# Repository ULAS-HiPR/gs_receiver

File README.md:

# Groundstation

Groundstation is the receiver/display side of the Ogma system. It is not part of the flight stack itself; it receives telemetry from Ogma and gives the operator a local display. The longer-term plan is for Ogma Console to switch into groundstation mode when this board is connected to a laptop.

## Role In Ogma

- Receives telemetry from the flight stack radio path.
- Displays useful field data locally.
- Provides a future high-detail laptop telemetry view through Ogma Console.

## Current Firmware

Current firmware is CircuitPython code in `firmware/`:

- `code.py`: main display loop.
- `gps_data.py`: GPS data container/parser.
- `screens.py`: ST7789 display screens for GPS/radio status.
- `sx1272.py`: polling SX1272 receive driver.
- `telemetry_protocol.py`: CRC-checked Ogma radio protocol decoder.

The receiver decodes Teachtaire protocol v1, updates the local GPS display, and prints USB serial lines directly consumable by Ogma Console:

- GPS as JSONL.
- CAN as `123#AABBCC...`.
- receiver diagnostics as ignored `#OGMA` comments.

PCB pin map used by firmware: shared SPI, TFT CS/DC/reset `D5/D4/D10`, radio CS/reset `D9/D2`, radio RX/TX switches `A0/A1`.

## Hardware

The repo contains hardware for:

- mobile receiver board,
- SPI display adapter,
- UART adapter.

## Ogma Console Support

Ogma Console can capture mixed GPS/CAN telemetry from the board's CircuitPython USB serial port, decode canonical CAN frames, plot telemetry, and save local bundles. Hardware RF/USB validation remains in the HIL campaign.

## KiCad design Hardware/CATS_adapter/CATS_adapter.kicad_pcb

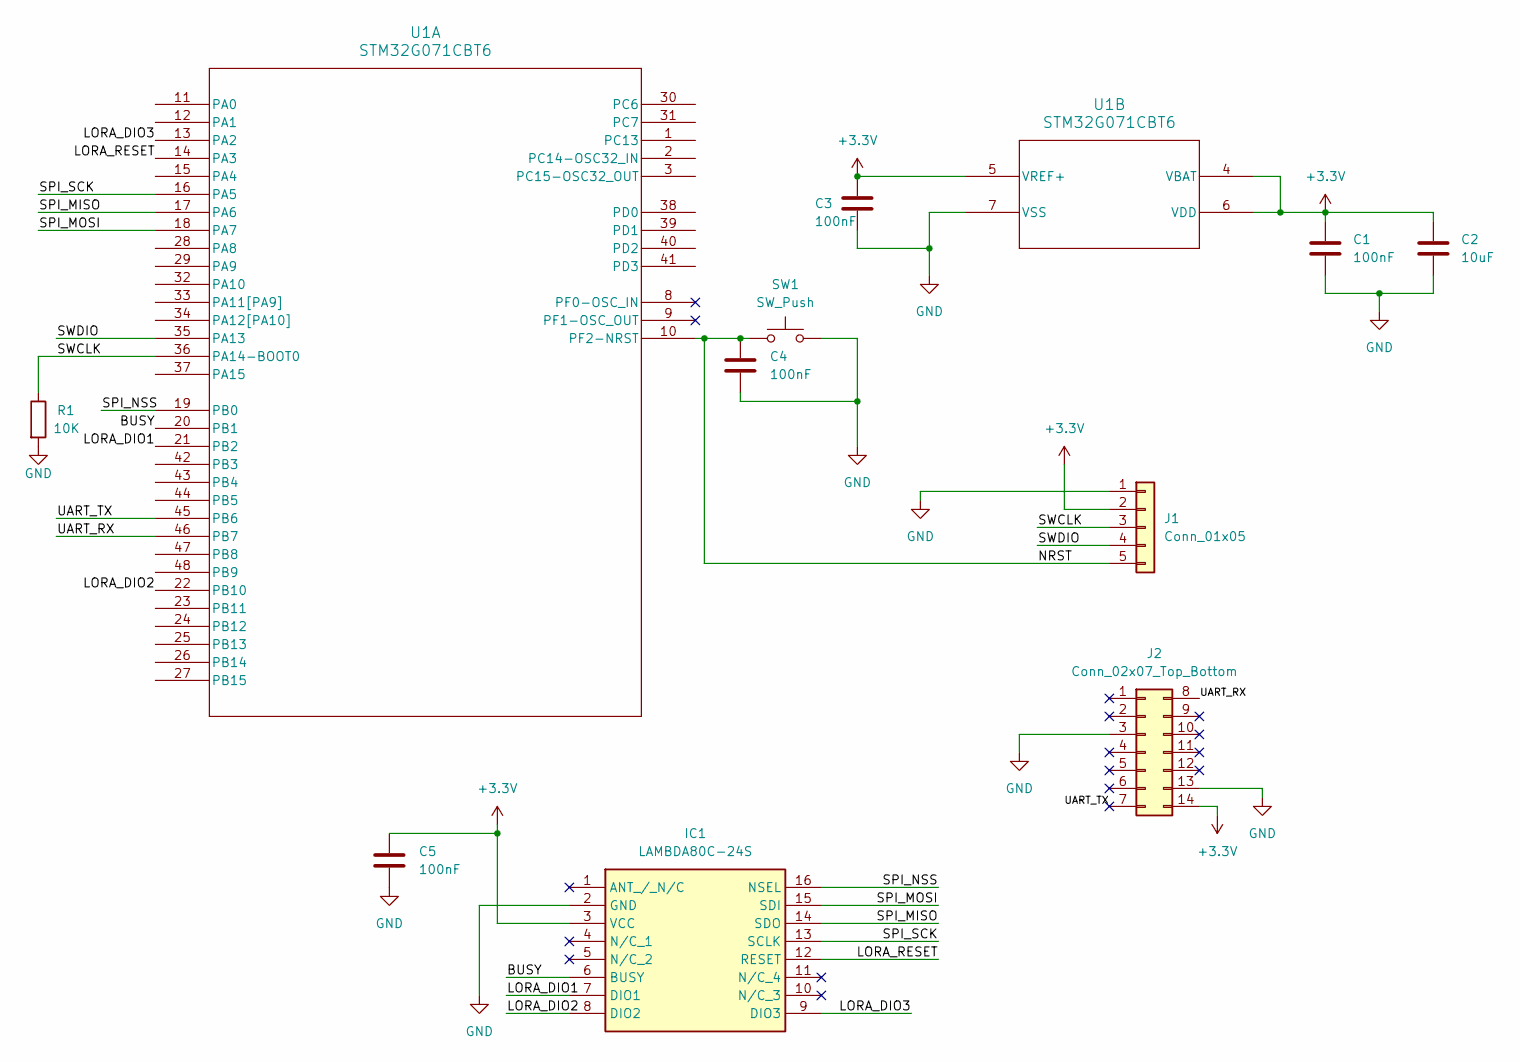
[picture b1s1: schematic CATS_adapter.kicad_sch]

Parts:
C1, C3, C4, C5: 100nF; C_0805_2012Metric_Pad1.18x1.45mm_HandSolder
C2: 10uF; C_0805_2012Metric_Pad1.18x1.45mm_HandSolder
IC1: LAMBDA80C-24S; LAMBDA80C24S; Mouser Part Number 223-LAMBDA80C-24S
J1: Conn_01x05; PinHeader_1x05_P2.54mm_Vertical
J2: Conn_02x07_Top_Bottom; PinHeader_2x07_P2.54mm_Horizontal
R1: 10K; R_0805_2012Metric_Pad1.20x1.40mm_HandSolder
SW1: SW_Push; SW_Push_1P1T_NO_E-Switch_TL3301NxxxxxG
U1: STM32G071CBT6; LQFP-48_7x7mm_P0.5mm

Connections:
+3.3V: C1.1, C2.1, C3.1, C5.1, IC1.3 (VCC), J1.2, J2.14, U1.4 (VBAT), U1.5 (VREF+), U1.6 (VDD)
/BUSY: IC1.6 (BUSY), U1.20 (PB1)
/LORA_DIO1: IC1.7 (DIO1), U1.21 (PB2)
/LORA_DIO2: IC1.8 (DIO2), U1.22 (PB10)
/LORA_DIO3: IC1.9 (DIO3), U1.13 (PA2)
/LORA_RESET: IC1.12 (RESET), U1.14 (PA3)
/NRST: C4.1, J1.5, SW1.1, U1.10 (PF2-NRST)
/SPI_MISO: IC1.14 (SDO), U1.17 (PA6)
/SPI_MOSI: IC1.15 (SDI), U1.18 (PA7)
/SPI_NSS: IC1.16 (NSEL), U1.19 (PB0)
/SPI_SCK: IC1.13 (SCLK), U1.16 (PA5)
/SWCLK: J1.3, R1.1, U1.36 (PA14-BOOT0)
/SWDIO: J1.4, U1.35 (PA13)
/UART_RX: J2.8, U1.46 (PB7)
/UART_TX: J2.7, U1.45 (PB6)
GND: C1.2, C2.2, C3.2, C4.2, C5.2, IC1.2 (GND), J1.1, J2.3, J2.13, R1.2, SW1.2, U1.7 (VSS)

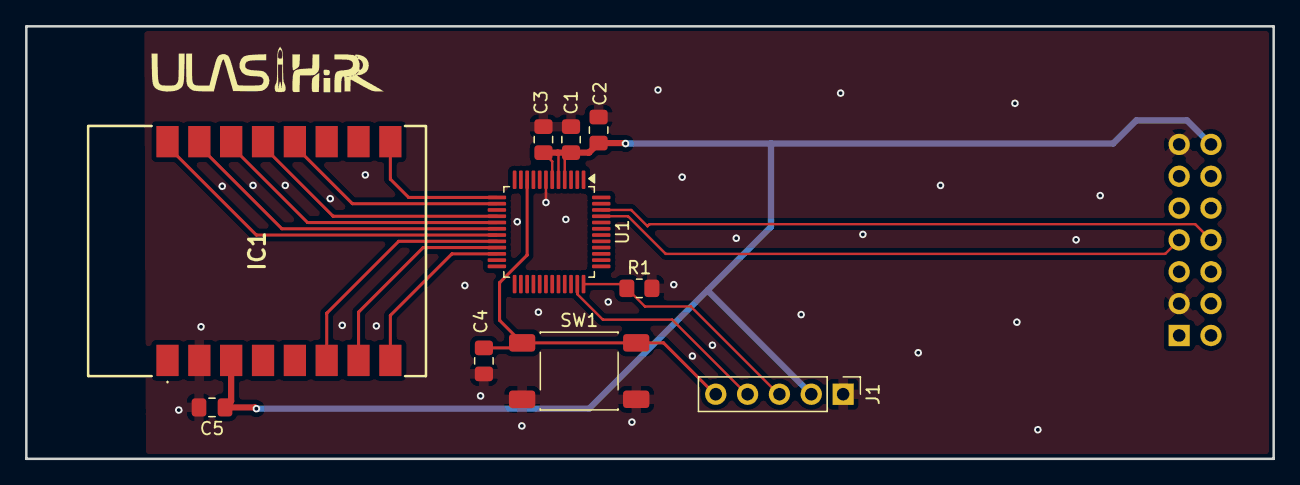
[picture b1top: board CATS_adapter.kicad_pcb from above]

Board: 2 copper layers, 99.5 x 34.5 mm, 11 parts (1 on the bottom side), 16 nets.

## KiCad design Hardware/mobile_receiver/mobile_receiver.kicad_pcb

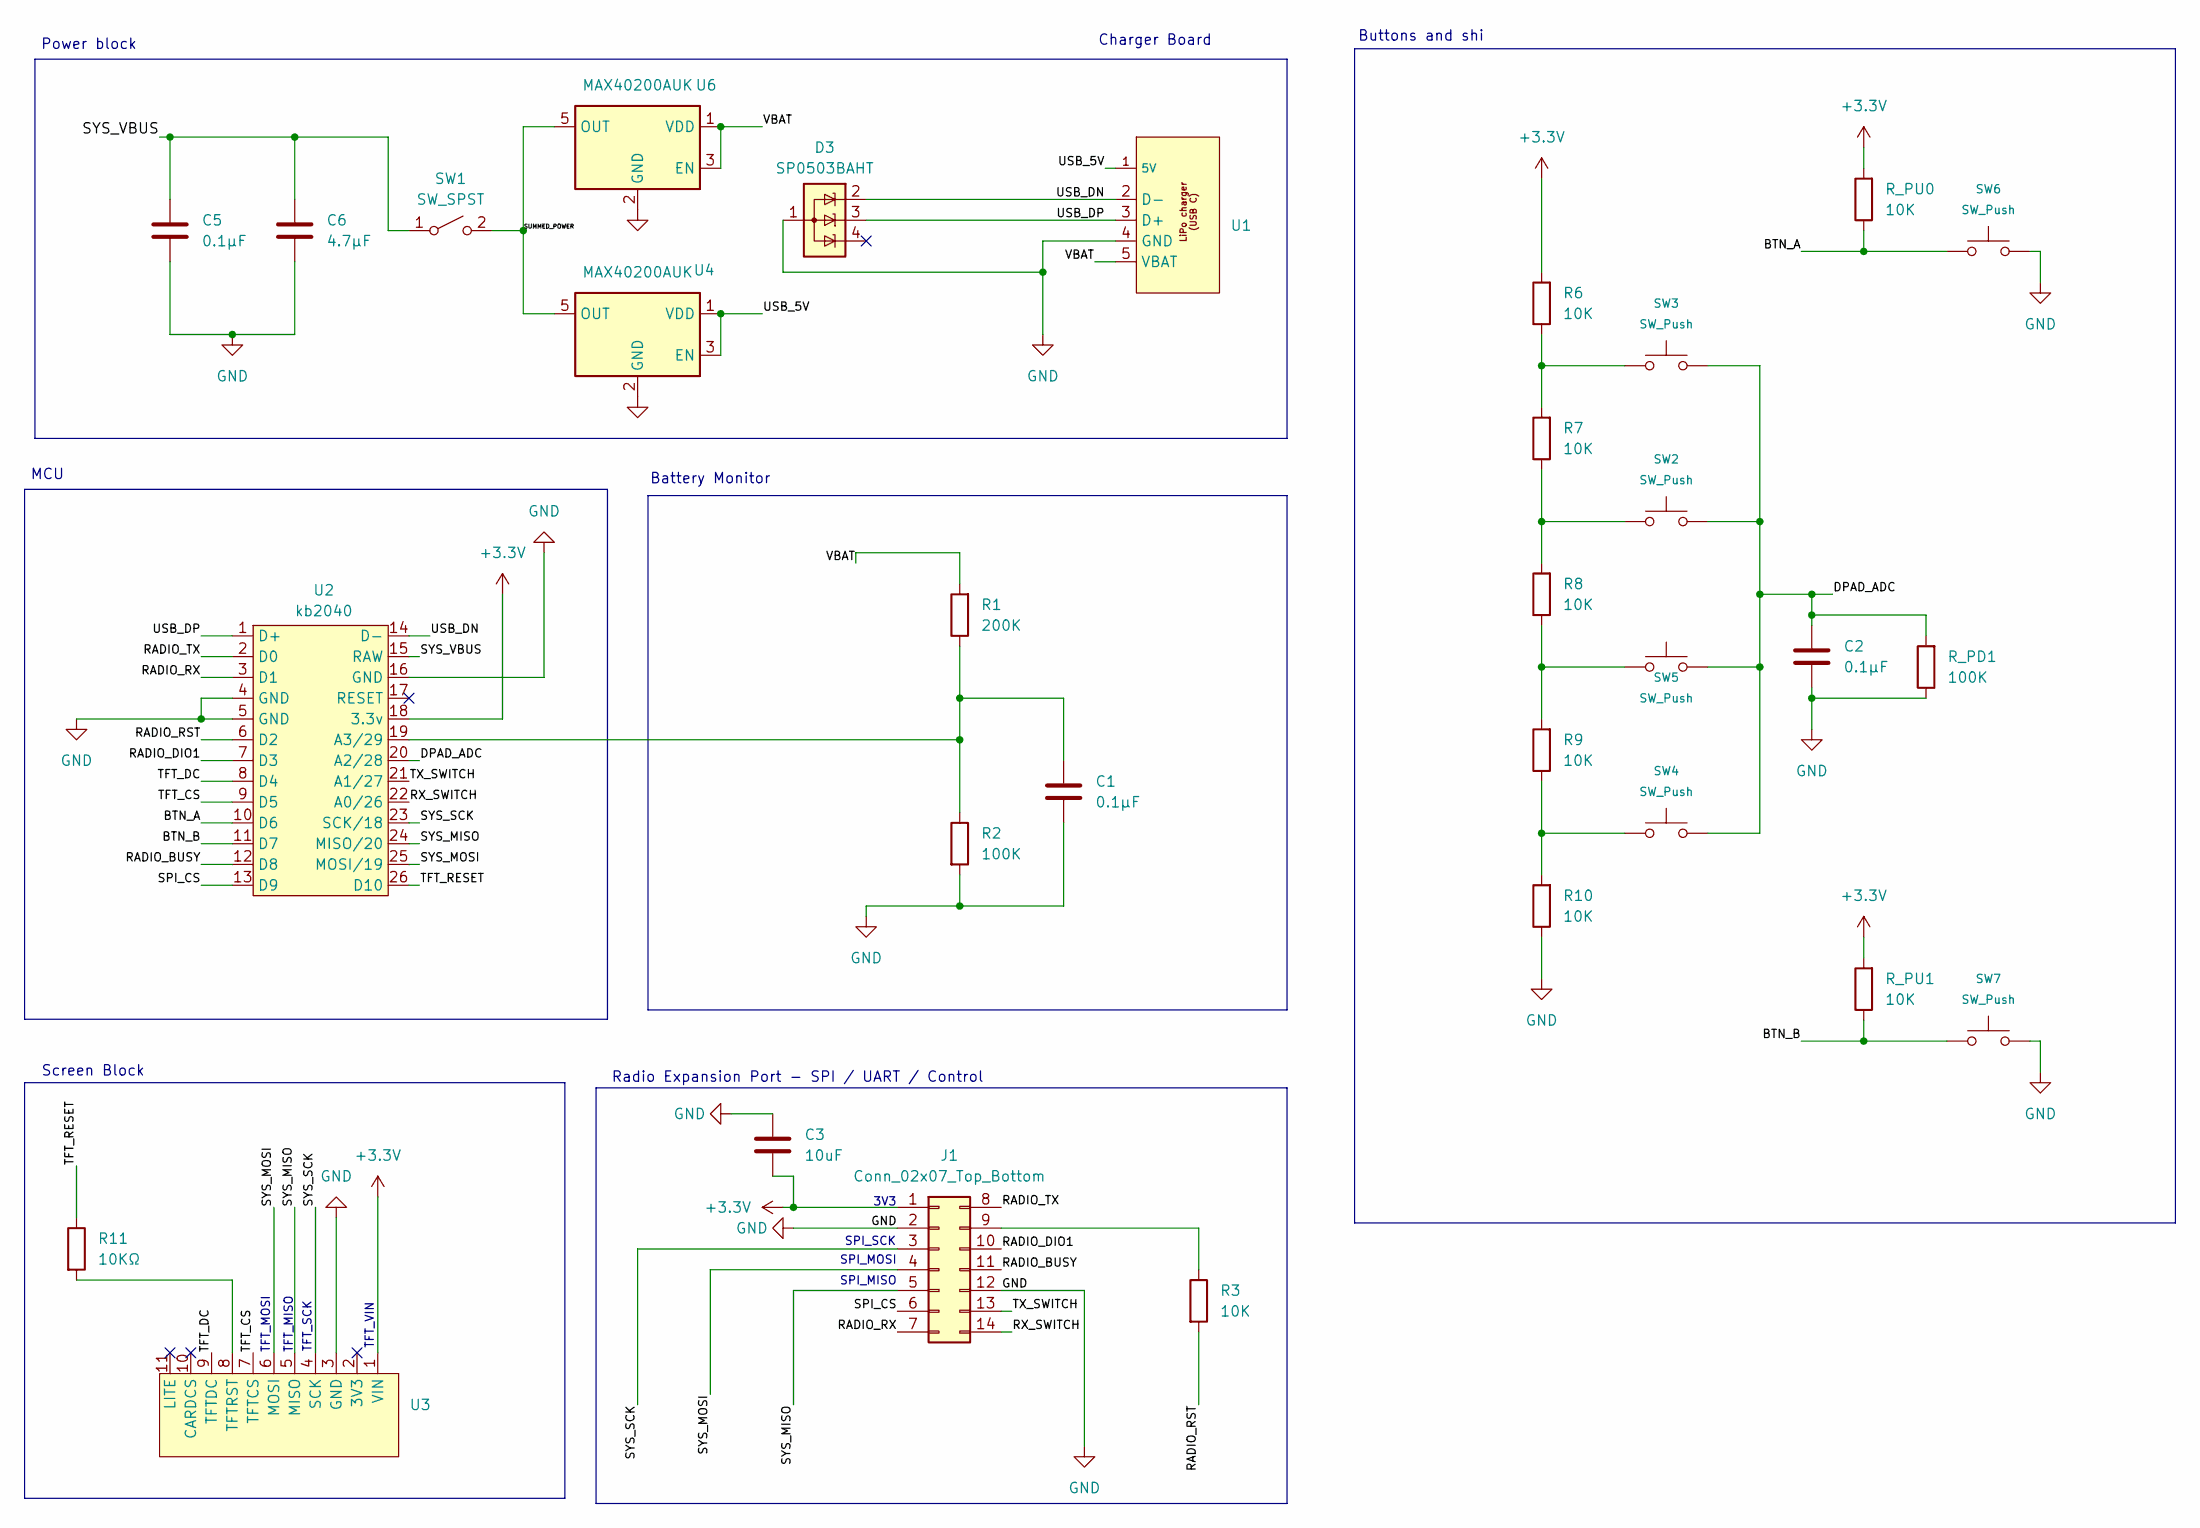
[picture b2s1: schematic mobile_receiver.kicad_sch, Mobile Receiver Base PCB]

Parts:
C1, C2, C5: 0.1µF; C_0805_2012Metric_Pad1.18x1.45mm_HandSolder
C3: 10uF; C_0805_2012Metric_Pad1.18x1.45mm_HandSolder
C6: 4.7µF; C_0805_2012Metric_Pad1.18x1.45mm_HandSolder
D3: SP0503BAHT; SOT-143
J1: Conn_02x07_Top_Bottom; PinSocket_2x07_P2.54mm_Horizontal
R1: 200K; R_0805_2012Metric_Pad1.20x1.40mm_HandSolder
R2: 100K; R_0805_2012Metric_Pad1.20x1.40mm_HandSolder
R3, R6, R7, R8, R9, R10: 10K; R_0805_2012Metric_Pad1.20x1.40mm_HandSolder
R11: 10KΩ; R_0805_2012Metric_Pad1.20x1.40mm_HandSolder
R_PD1: 100K; R_0805_2012Metric_Pad1.20x1.40mm_HandSolder
R_PU0, R_PU1: 10K; R_0805_2012Metric_Pad1.20x1.40mm_HandSolder
SW1: SW_SPST; OS102011MA1QN1_CNK
SW2, SW3, SW4, SW5, SW6, SW7: SW_Push; SW_Push_1P1T_NO_E-Switch_TL3301NxxxxxG
U1: 4410_Micro_LiPo_USBC
U2: kb2040
U3: Adafruit_280X240_Display
U4, U6: MAX40200AUK; SOT-23-5

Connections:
+3.3V: C3.2, J1.1, R6.2, R_PU0.2, R_PU1.2, U2.18 (3.3v), U3.1 (VIN)
/BTN_A: R_PU0.1, SW6.1, U2.10 (D6)
/BTN_B: R_PU1.1, SW7.1, U2.11 (D7)
/DPAD_ADC: C2.1, R_PD1.2, SW2.2, SW3.2, SW4.2, SW5.2, U2.20 (A2/28)
/RADIO_BUSY: J1.11, U2.12 (D8)
/RADIO_DIO1: J1.10, U2.7 (D3)
/RADIO_RST: R3.2, U2.6 (D2)
/RADIO_RX: J1.7, U2.3 (D1)
/RADIO_TX: J1.8, U2.2 (D0)
/RX_SWITCH: J1.14, U2.22 (A0/26)
/SPI_CS: J1.6, U2.13 (D9)
/SUMMED_POWER: SW1.2 (B), U4.5 (OUT), U6.5 (OUT)
/SYS_MISO: J1.5, U2.24 (MISO/20), U3.5 (MISO)
/SYS_MOSI: J1.4, U2.25 (MOSI/19), U3.6 (MOSI)
/SYS_SCK: J1.3, U2.23 (SCK/18), U3.4 (SCK)
/SYS_VBUS: C5.1, C6.1, SW1.1 (A), U2.15 (RAW)
/TFT_CS: U2.9 (D5), U3.7 (TFTCS)
/TFT_DC: U2.8 (D4), U3.9 (TFTDC)
/TFT_RESET: R11.1, U2.26 (D10)
/TX_SWITCH: J1.13, U2.21 (A1/27)
/USB_5V: U1.1 (5V), U4.1 (VDD), U4.3 (EN)
/USB_DN: D3.2 (K), U1.2 (D-), U2.14 (D-)
/USB_DP: D3.3 (K), U1.3 (D+), U2.1 (D+)
/VBAT: R1.2, U1.5 (VBAT), U6.1 (VDD), U6.3 (EN)
GND: C1.2, C2.2, C3.1, C5.2, C6.2, D3.1 (A), J1.2, J1.12, R2.2, R10.1, R_PD1.1, SW6.2, SW7.2, U1.4 (GND), U2.4 (GND), U2.5 (GND), U2.16 (GND), U3.3 (GND), U4.2 (GND), U6.2 (GND)
unnamed: J1.9, R3.1
unnamed: R6.1, R7.2, SW3.1
unnamed: R7.1, R8.2, SW2.1
unnamed: R8.1, R9.2, SW5.1
unnamed: R9.1, R10.2, SW4.1
unnamed: C1.1, R1.1, R2.1, U2.19 (A3/29)
unnamed: R11.2, U3.8 (TFTRST)

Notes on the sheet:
TFT_MOSI
Radio Expansion Port - SPI / UART / Control
3V3
Screen Block
TFT_SCK
MCU
Buttons and shi
TFT_MISO
TFT_VIN
Battery Monitor
SPI_MOSI
SPI_SCK
Charger Board
SPI_MISO
Power block

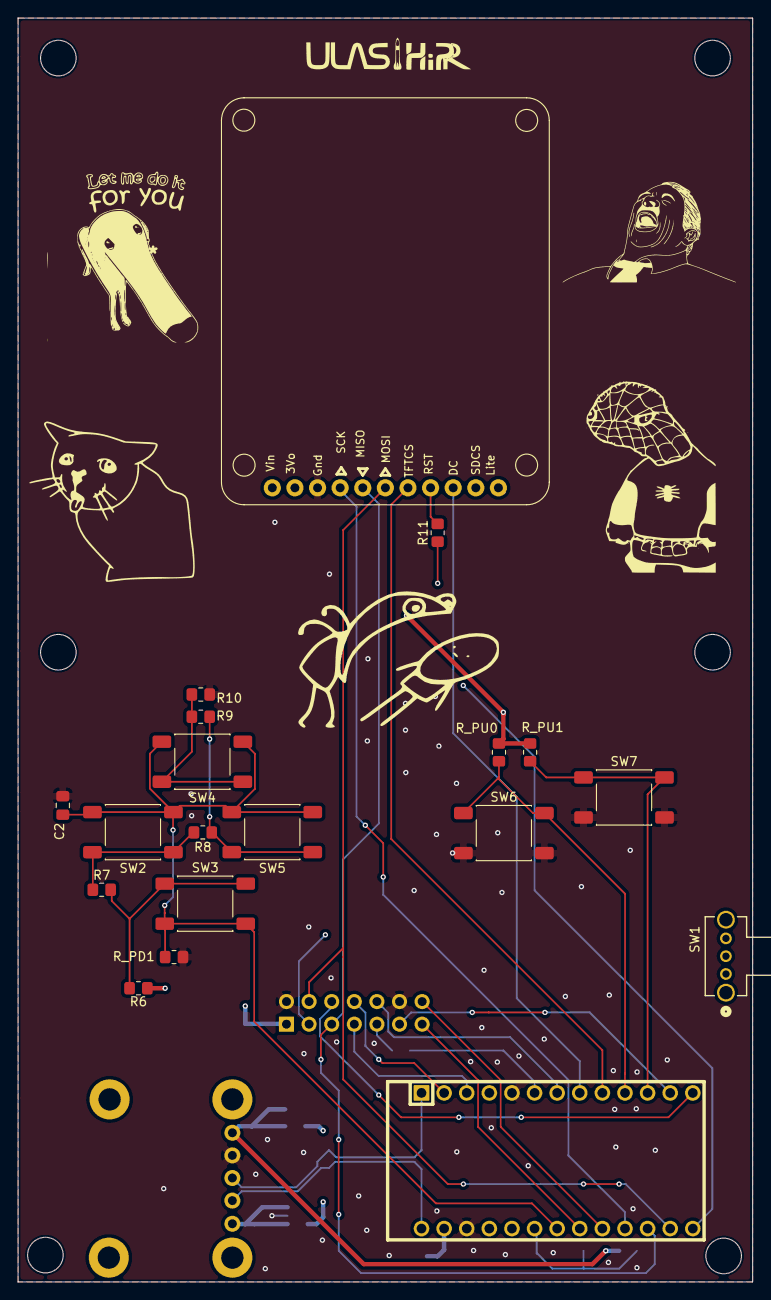
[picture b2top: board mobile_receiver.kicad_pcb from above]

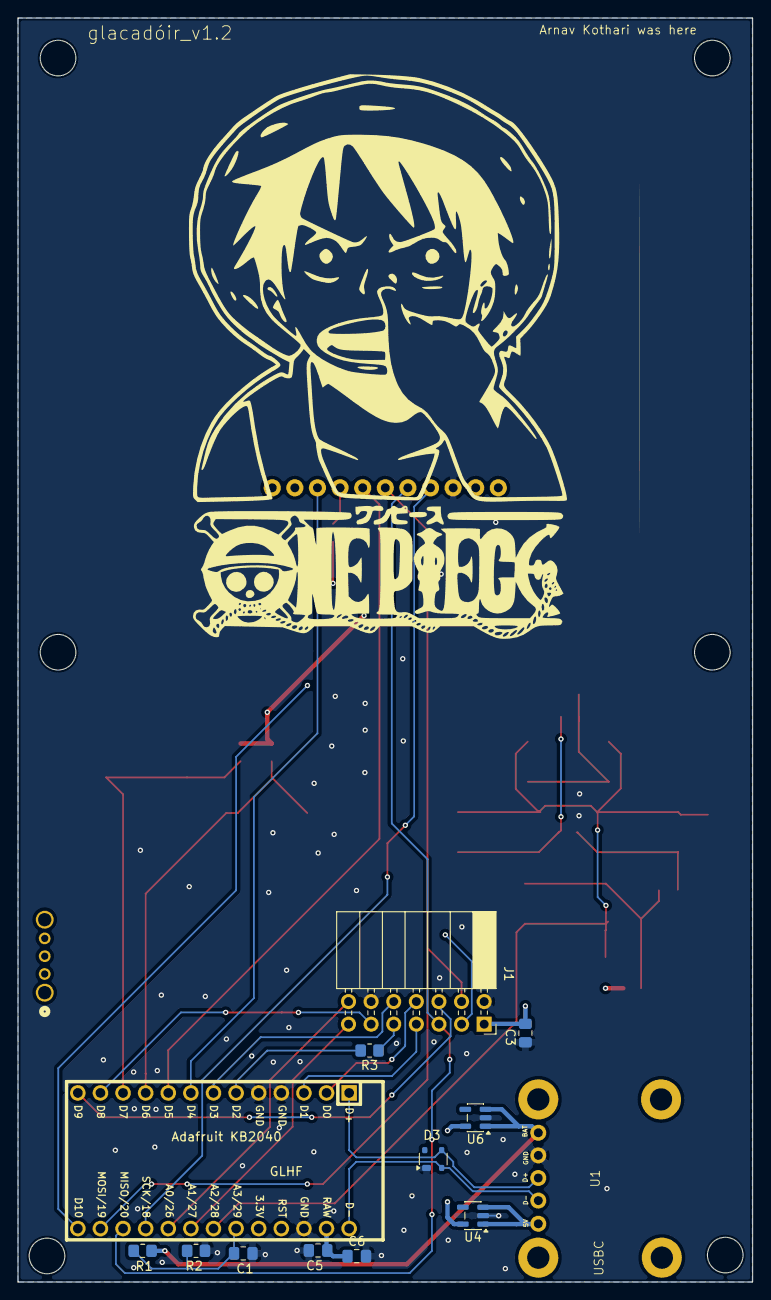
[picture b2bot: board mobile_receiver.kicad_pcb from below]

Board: 4 copper layers, 82.5 x 142.0 mm, 31 parts (13 on the bottom side), 32 nets.

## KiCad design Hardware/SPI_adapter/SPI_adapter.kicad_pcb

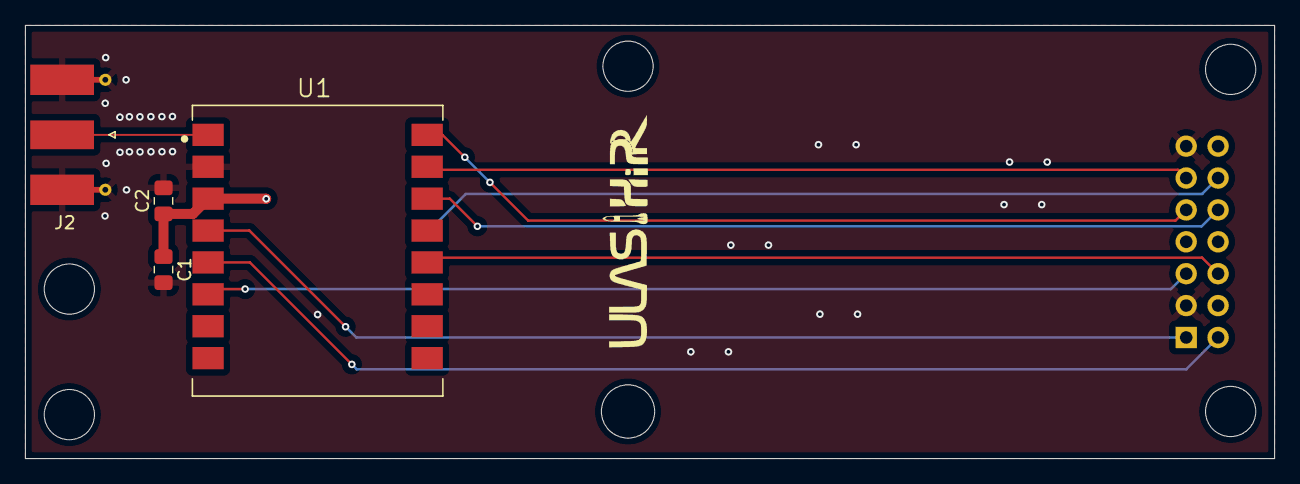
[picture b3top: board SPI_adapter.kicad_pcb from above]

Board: 4 copper layers, 99.5 x 34.5 mm, 5 parts (1 on the bottom side), 11 nets.

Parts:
C1: 100nF; C_0805_2012Metric_Pad1.18x1.45mm_HandSolder
C2: 4.7µF; C_0805_2012Metric_Pad1.18x1.45mm_HandSolder
J1: Conn_02x07_Top_Bottom; PinHeader_2x07_P2.54mm_Horizontal
J2: Conn_Coaxial; SMA_Molex_73251-1153_EdgeMount_Horizontal
U1: RF-LORA-868-SO; XCVR_RF-LORA-868-SO

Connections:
+3.3V: C1.1, C2.1, J1.14, U1.3 (VCC)
/RADIO_DIO1: J1.5, U1.6 (DIO0)
/RADIO_RST: J1.6, U1.12 (RESET)
/RF_ANT: J2.1 (In), U1.1 (ANT)
/RX_SWITCH: J1.1, U1.4 (RX_SWITCH)
/SPI_CS: J1.9, U1.16 (~SEL)
/SPI_MISO: J1.10, U1.14 (SDO)
/SPI_MOSI: J1.11, U1.15 (SDI)
/SPI_SCK: J1.12, U1.13 (SCLK)
/TX_SWITCH: J1.2, U1.5 (TX_SWITCH)
GND: C1.2, C2.2, J1.3, J1.13, J2.2 (Ext), U1.2 (GND)

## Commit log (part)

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2026-02-08 Adding base code
2026-02-23 Added hardware kicad files
    Added designs for main board, SPI adapter and the UART adapter (which is in progress)
2026-02-23 Fixed Board stack up and RF trace for SPI adapter
2026-02-24 Fixed USB traces, radio connectors, finished UART adapter
2026-02-24 Added new Switch
2026-02-24 Added manufacturing files and CAD
    ZIP format
2026-02-28 Update to latest version
2026-02-28 Refined Stitching Vias
2026-02-28 Refined Trace Jumps
2026-02-28 Saved Push
2026-02-28 Vias and trace spacing
2026-02-28 Updated package sizes
2026-02-28 Saved the previous update in kicad
2026-02-28 Tactile Buttons Replaced
2026-03-01 Updated traces and vias according to new switches and passives
2026-03-01 Fixed RF trace, Added new Diodes, better power traces and new switches
2026-03-02 adding fixed screen
2026-03-02 Updated eggfinder to correct wiring
2026-03-02 Added HiPR logos and fixed mounting wholes
2026-03-03 SPI resistors removed and transmission added
2026-03-31 hardware done
2026-04-02 cleaning up screen code
2026-04-02 adding git ignore
2026-04-02 Copied from hardware_done and removed DS_strore file
2026-05-30 Code updated
2026-06-17 Eggtimer working code
